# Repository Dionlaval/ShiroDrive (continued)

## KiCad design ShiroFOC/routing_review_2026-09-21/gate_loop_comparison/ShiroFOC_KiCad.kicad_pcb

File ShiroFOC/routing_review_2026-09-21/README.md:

# Routing review checkpoint — 21 September 2026

**Paused for the user's visual review. Nothing here is a finished PCB.** Original P0, P1 placement and all routing candidates are preserved. No more routing changes should be made until the user provides their hint or asks to resume.

## Which board to open

| Project folder | Purpose | Unconnected items | Other error-severity DRC violations |
|---|---|---:|---:|
| `latest_trial` | Latest placement/corridor experiment; open this first | 152 | 0 |
| `best_baseline` | Most complete checked connectivity before the corridor reset | 91 | 0 |
| `gate_loop_comparison` | Seven gate/reference connections, but some outgoing/return routes form large loops; comparison only | 149 | 0 |

Open `ShiroFOC_KiCad.kicad_pro` or `.kicad_pcb` in each folder. Each includes the schematic hierarchy, local libraries, board rules and native DRC checkpoint. Counts refer to KiCad's unconnected **items**, not distinct nets. Zero other errors does not mean clean DRC: all boards remain incomplete and have warnings.

## Most useful area to examine

The corridor from U301's upper/right gate-driver pins to Q401/Q402/Q403 and their gate resistors. In native KiCad coordinates this is approximately **X 137–170 mm, Y 128–164 mm** (board-local X 37–70, Y 28–64).

- Highlight **GHS1 + OUT1**, **GHS2 + OUT2**, and **GHS3 + OUT3** in turn. Each high-side gate signal needs its matching phase-reference return close by.
- Check the remaining **GLS1/2/3** routes alongside their source/ground return environment.
- The six **SHUNT_*_SENSE_P/N** traces and underside ratio networks are already connected; preserve their Kelvin pickoff and avoid routing gate signals alongside them for long distances.
- Examine C412/C422/C432 and the adjacent source/shunt via banks on both faces. A passage that appears open on top may be blocked underneath.
- Preserve the wide **VM** feed and the **FORCE_P** / shunt / GND current paths. A route that cuts their only useful copper bridge is not an acceptable improvement.

A useful hint would be a preferred routing corridor, a different ordering of these paths, or a suggested relocation of the MCU-side parts / phase-cell passives. No need to solve all remaining ordinary signals.

## What the latest trial contains

- Ordinary unlocked routes around the driver corridor were removed deliberately. This explains the higher unconnected count than the baseline.
- R301 and C306 moved to open an underside corridor; R602 retained at the earlier clean location. GHS1/GHS3 outward fanouts and additional driver fanouts remain.
- C412/C422/C432 were rotated horizontally; their VM/GND via arrangements changed. Six gate resistors moved 0.2 mm sideways to maintain component courtyards.
- Local 0.20 mm clearance regions were added around those populated capacitor/gate-resistor areas. Existing global and MCU/package rules remain.
- The middle-phase reference route was previously trapped. It now has a roughly 23.5 mm new connecting path. All three OUT reference connections are present in this latest trial, but their matching gate routes still need to be established as close pairs.
- Remaining warnings include narrow copper connections around the revised via arrays, dangling items and inherited silk/library warnings. These have **not** been accepted as final.

## Why routing is paused

Repeated shortest-path routing was reducing connectivity counts without preserving gate-return geometry. Some routes were rejected for 90–154 mm detours; others connected successfully but created large loops or isolated power copper. The experiments found specific placement bottlenecks, but a visual hint is now more efficient than another automatic iteration.

## Still outstanding after the hint

Finish paired gate routing and ordinary signals; restore/check bus copper continuity and ground stitching; recheck native DRC and schematic/PCB parity; perform the critical return-path/EMI/thermal review; implement low-tradeoff high-priority fixes; produce the requested actual-PCB wireframe and colour-coded routing presentation. External fabricator and component-availability checks remain excluded as requested.

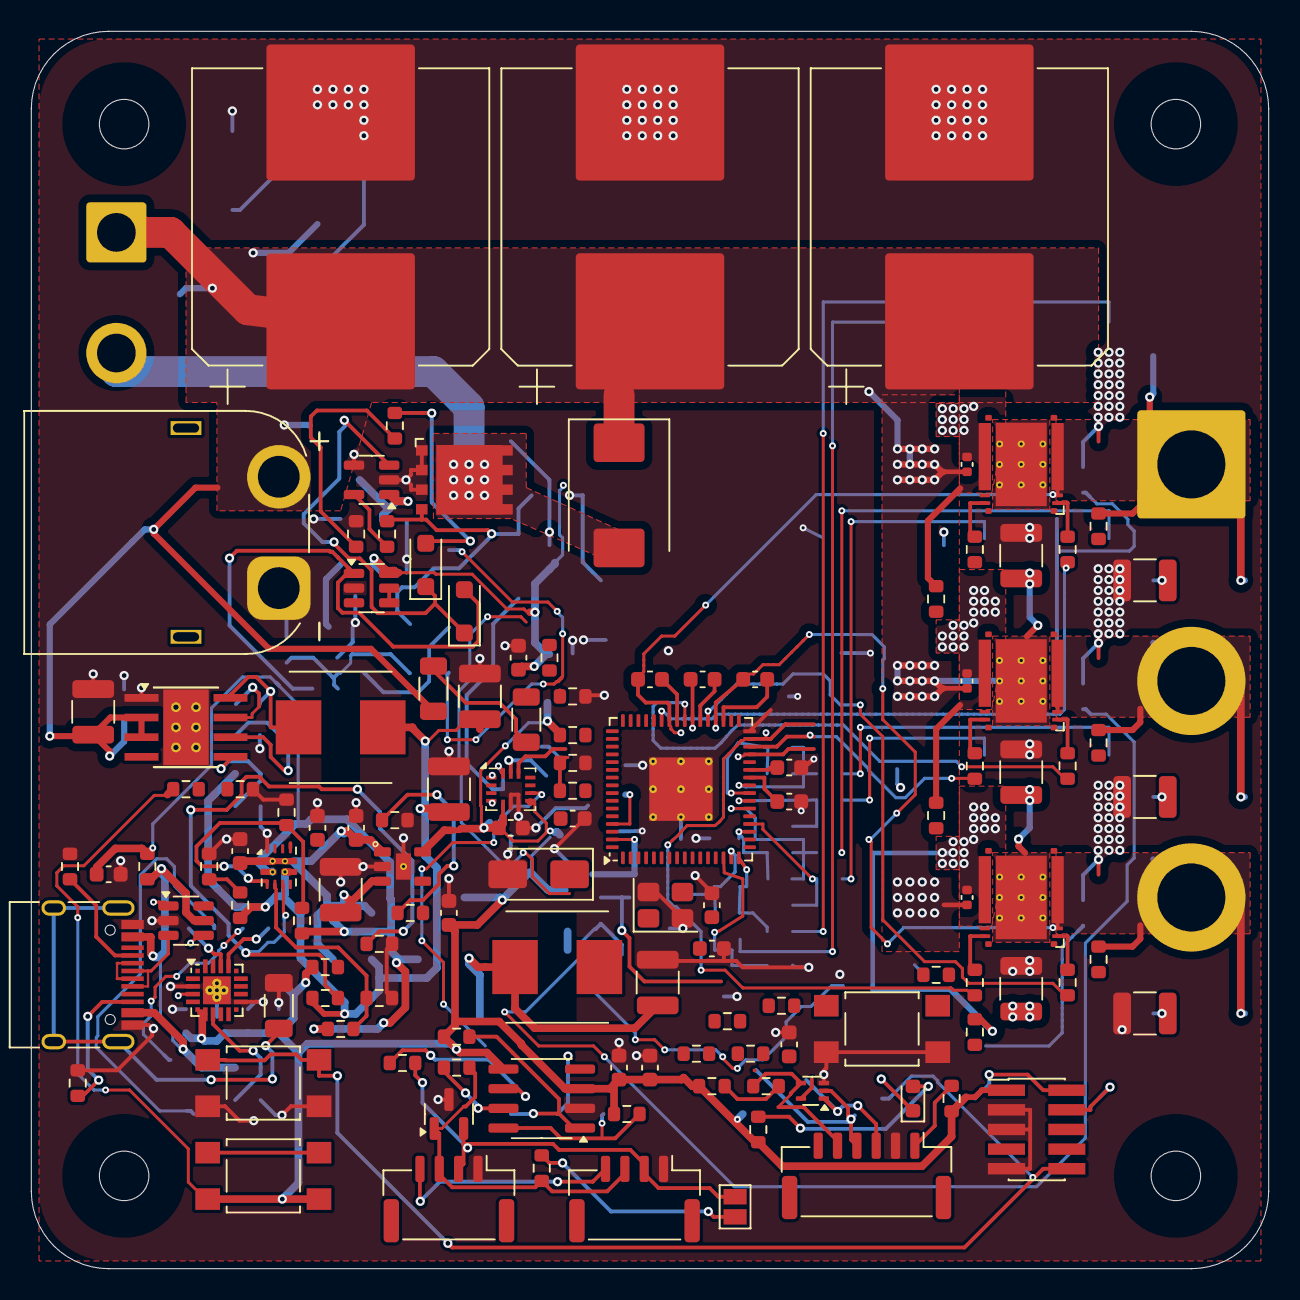
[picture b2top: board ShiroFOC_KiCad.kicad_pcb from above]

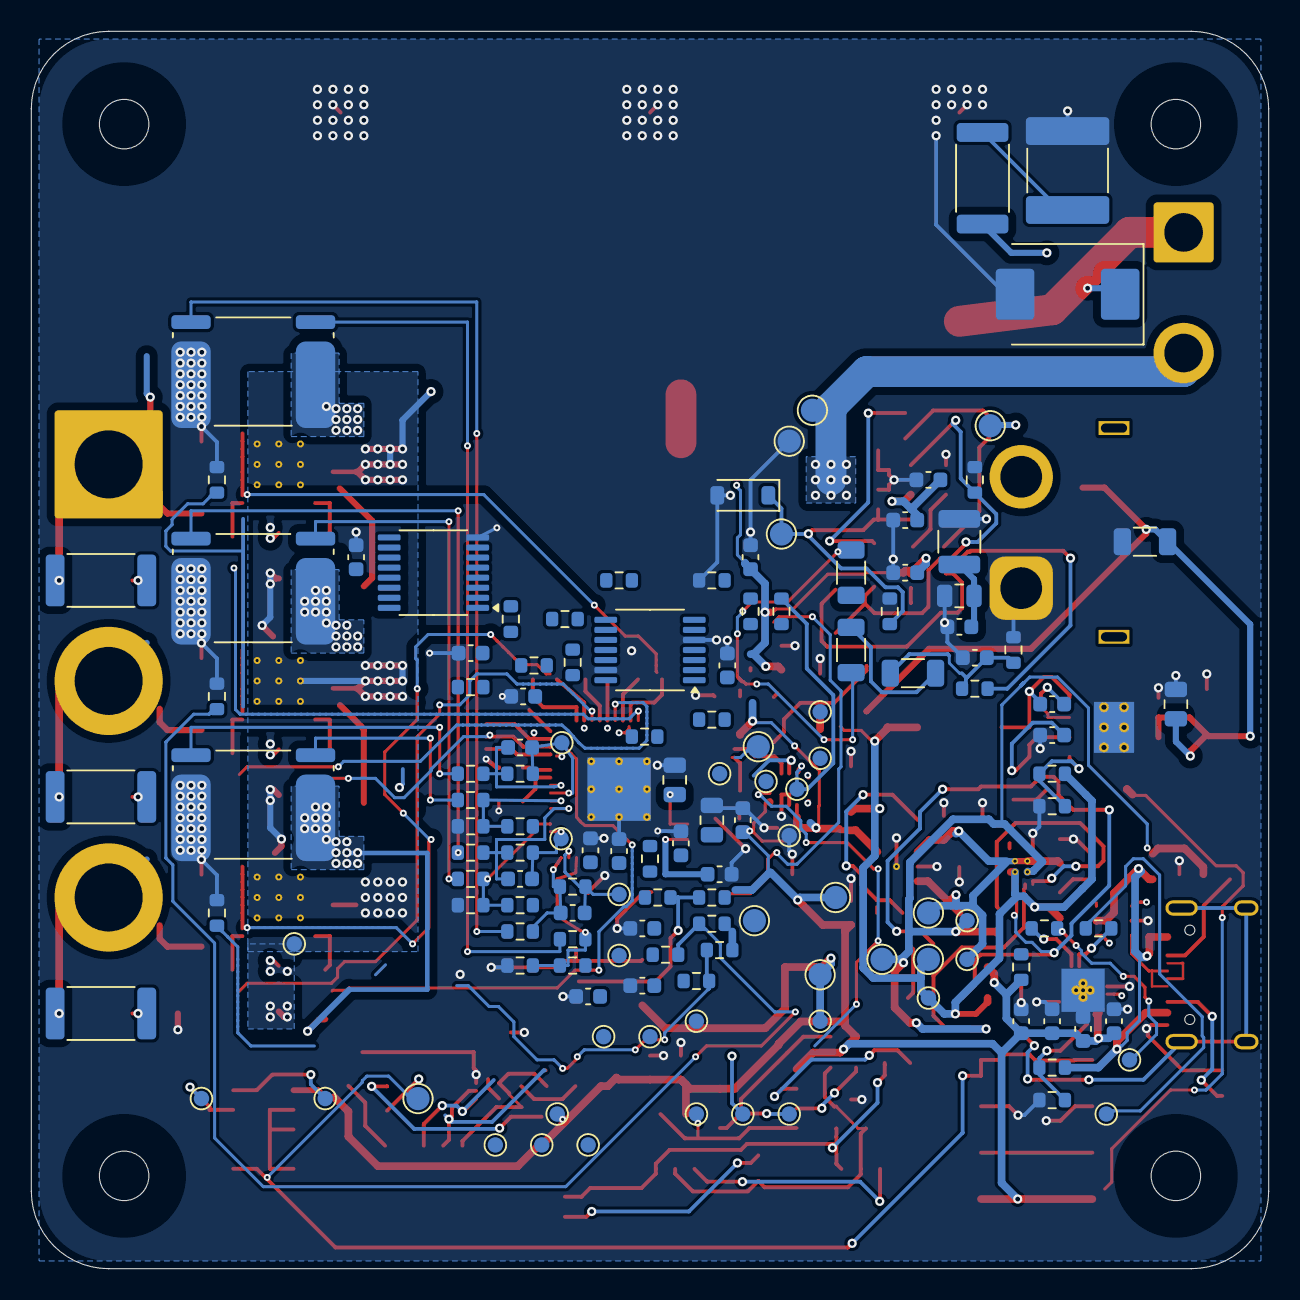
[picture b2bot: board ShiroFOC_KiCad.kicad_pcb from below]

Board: 4 copper layers, 80.0 x 80.0 mm, 264 parts (136 on the bottom side), 148 nets.

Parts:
C101, C102, C103: 680uF 63V; CP_Elec_18x17.5
C104: 4.7uF 100V X7R; C_1210_3225Metric
C105: 100nF 100V X7R; C_0805_2012Metric
C106: 10nF 100V C0G; C_0603_1608Metric
C107: RC DAMP C - TUNE; C_2220_5750Metric
C108, C314, C711, C712, C713: 10nF; C_0603_1608Metric
C201: 2.2uF 100V X7R; C_1210_3225Metric
C202: 220nF 100V X7R; C_0805_2012Metric
C203, C209, C211, C301, C303, C305, C307, C310, C503, C601, C603, C701, C702, C801, C902, C904: 100nF; C_0603_1608Metric
C204, C304, C306, C602, C802: 1uF; C_0603_1608Metric
C205, C206, C210: 22uF 10V X7R; C_1210_3225Metric
C207: 4.7nF 2kV; C_1206_3216Metric
C208: 1uF 10V; C_0603_1608Metric
C212, C213: 2.2uF 10V X7R; C_0603_1608Metric
C302: 10uF 10V; C_0805_2012Metric
C308, C309: 10pF C0G; C_0603_1608Metric
C311: 220nF 100V; C_0805_2012Metric
C312: 10uF 25V X7R; C_1210_3225Metric
C313, C411, C421, C431, C502: 100nF 25V; C_0603_1608Metric
C412, C422, C432: 1uF 100V X7R; C_1210_3225Metric
C413, C423, C433: SNUBBER C TUNE; C_1210_3225Metric
C414, C424, C434: 47pF C0G; C_0603_1608Metric
C415, C425, C435: 10nF 100V X7S; C_0402_1005Metric
C501: 1uF 25V; C_0603_1608Metric
C504: 1nF C0G; C_0603_1608Metric
C604: 100nF 50V; C_0603_1608Metric
C901, C903: 4.7uF 10V; C_0603_1608Metric
D101: VM TVS - SELECT AFTER TEST; D_SMC
D301: RED; LED_0603_1608Metric
D302: STPS1H100A; D_SMA
D501: BZT52C12 12V; D_SOD-123
D502, D503: BAT54H; D_SOD-123F
D504: B5100C 100V 5A; D_SMC
D601: TPD3E001DRLR 3-line ESD; Texas_R-PDSO-N5_DRL-5
D801: PESD2CANFD24V-T; SOT-23
H1, H2, H3, H4: M3 NPTH; MountingHole_3.2mm_M3
J101: AMASS XT60PW-M; AMASS_XT60PW-M_1x02_P7.20mm_Horizontal
J201: USB-C service; USB_C_Receptacle_HRO_TYPE-C-31-M-12
J401: MOTOR U/V/W; SolderWire-6sqmm_1x03_P14mm_D3.5mm_OD7mm
J501: BRAKE RESISTOR; SolderWire-2sqmm_1x02_P7.8mm_D2mm_OD3.9mm
J601: EXT ENCODER / HALL; JST_GH_BM06B-GHS-TBT_1x06-1MP_P1.25mm_Vertical
J801: CAN 1; JST_GH_BM04B-GHS-TBT_1x04-1MP_P1.25mm_Vertical
J802: CAN 2; JST_GH_BM04B-GHS-TBT_1x04-1MP_P1.25mm_Vertical
J1001: ARM Cortex SWD 10-pin; PinHeader_2x05_P1.27mm_Vertical_SMD
JP801: TERM ENABLE; SolderJumper-2_P1.3mm_Open_Pad1.0x1.5mm
L201, L301: 22uH / 2.75A; WE_LHMI_7050_74437349220
Q401, Q402, Q403: CSD88599Q5DC; CSD88599Q5DC_DMM0022A
Q501: CSD19531Q5A 100V; CSD19531Q5A_Q5A_DQJ0008A
R101: 470k 0.25W; R_1206_3216Metric
R102: RC DAMP R - TUNE; R_2512_6332Metric
R103, R104: 270k 0.1% 100V; R_1206_3216Metric
R105: 27k 0.1%; R_0603_1608Metric
R106, R304, R312, R711, R712, R713, R901, R1001: 1k; R_0603_1608Metric
R201: 100k 1%; R_0603_1608Metric
R202: 24.9k 1%; R_0603_1608Metric
R203, R204: 5.1k; R_0603_1608Metric
R205, R301, R302, R412, R422, R432: 0R; R_0603_1608Metric
R206: 15.0k 1%; R_0603_1608Metric
R207, R209, R211, R213: 5.10k 1%; R_0603_1608Metric
R208: 10.0k 1%; R_0603_1608Metric
R210, R212: 21.0k 1%; R_0603_1608Metric
R214: 80.6k 1%; R_0603_1608Metric
R215, R305, R306, R307, R308, R309, R311, R501, R504, R505, R801, R805: 10k; R_0603_1608Metric
R303, R310, R413, R414, R423, R424, R433, R434: 100k; R_0603_1608Metric
R313, R314: 22R; R_0603_1608Metric
R410, R420, R430, R441, R442, R443: 56k 0.1%; R_0603_1608Metric
R411, R421, R431, R503: 4.7R; R_0603_1608Metric
R415, R425, R435: SNUBBER R TUNE; R_2512_6332Metric
R416, R426, R436: BVR-Z-R0005 0.5mR; R_Shunt_Isabellenhuette_BVR4026
R417, R418, R427, R428, R437, R438: 1k 0.1%; R_0603_1608Metric
R419, R429, R439: 28k 0.1%; R_0603_1608Metric
R502, R601, R602, R603, R611, R714: 33R; R_0603_1608Metric
R506, R507, R508: 150k 0.1% 100V; R_1206_3216Metric
R509: 12.7k 0.1%; R_0603_1608Metric
R510: 1M 0.1%; R_0603_1608Metric
R604: 0R; external load <=25mA; R_0603_1608Metric
R605, R606, R607, R902, R903: 100R; R_0603_1608Metric
R608, R609, R610: 10k DNP Hall pull-up; R_0603_1608Metric
R701, R702, R703: 4.7k 1%; R_0603_1608Metric
R802: 120R 1%; R_0603_1608Metric
R803: 0R CANH link; R_0603_1608Metric
R804: 0R CANL link; R_0603_1608Metric
R904: 22.1k 1%; R_0603_1608Metric
R905: 47.5k 1%; R_0603_1608Metric
SW301, SW1002: RESET; SW_SPST_TL3305A
SW1001: BOOT0; SW_SPST_TL3305A
TH701, TH702, TH703: 10k NTC B3380; R_0603_1608Metric
TP101: VM; TestPoint_Pad_D1.5mm
TP102: GND; TestPoint_Pad_D1.5mm
TP103: VBUS_SENSE; TestPoint_Pad_D1.5mm
TP201: 5V_BAT; TestPoint_Pad_D1.5mm
TP202: 5V_USB; TestPoint_Pad_D1.5mm
TP203: 5V_SYS; TestPoint_Pad_D1.5mm
TP204: 3V3; TestPoint_Pad_D1.5mm
TP301: VCC; TestPoint_Pad_D1.5mm
TP302: SCREF; TestPoint_Pad_D1.5mm
TP303: NRST; TestPoint_Pad_D1.5mm
TP501: BRAKE_GATE; TestPoint_Pad_D1.5mm
TP502: BRK_SW; TestPoint_Pad_D1.5mm
TP701: NTC_A; TestPoint_Pad_D1.0mm
TP702: NTC_B; TestPoint_Pad_D1.0mm
TP703: NTC_C; TestPoint_Pad_D1.0mm
TP901: USB_UART_TX; TestPoint_Pad_D1.0mm
TP902: USB_UART_RX; TestPoint_Pad_D1.0mm
TP903: GND; TestPoint_Pad_D1.0mm
TP1001: VM; TestPoint_Pad_D1.0mm
TP1002: VCC; TestPoint_Pad_D1.0mm
TP1003: 5V_BAT; TestPoint_Pad_D1.0mm
TP1004: 5V_USB; TestPoint_Pad_D1.0mm
TP1005: 5V_SYS; TestPoint_Pad_D1.0mm
TP1006: 3V3; TestPoint_Pad_D1.0mm
TP1007: NRST; TestPoint_Pad_D1.0mm
TP1008: SWDIO; TestPoint_Pad_D1.0mm
TP1009: SWCLK; TestPoint_Pad_D1.0mm
TP1010: SPI3_SCK; TestPoint_Pad_D1.0mm
TP1011: SPI3_MISO; TestPoint_Pad_D1.0mm
TP1012: SPI3_MOSI; TestPoint_Pad_D1.0mm
TP1013: FDCAN1_TX; TestPoint_Pad_D1.0mm
TP1014: FDCAN1_RX; TestPoint_Pad_D1.0mm
TP1015: FEEDBACK_A_H1; TestPoint_Pad_D1.0mm
TP1016: FEEDBACK_B_H2; TestPoint_Pad_D1.0mm
TP1018: OPO_U1; TestPoint_Pad_D1.0mm
TP1019: OPO_V1; TestPoint_Pad_D1.0mm
TP1020: OPO_W1; TestPoint_Pad_D1.0mm
TP1021: SPARE_GPIO_1; TestPoint_Pad_D1.0mm
TP1022: CAN_STB; TestPoint_Pad_D1.0mm
TP1023: SPARE_GPIO_3; TestPoint_Pad_D1.0mm
TP1024: SPARE_TIM_GPIO; TestPoint_Pad_D1.0mm
U201: LMR36510FADDAR; Texas_HTSOP-8-1EP_3.9x4.9mm_P1.27mm_EP2.95x4.9mm_Mask2.4x3.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
U202: USBLC6-2SC6; SOT-23-6
U203: TPS2121RUXR; Texas_VQFN-HR-12_2x2.5mm_P0.5mm_ThermalVias
U204: TLV75533PDYDR; Texas_DYD0005A_SOT23-5
U301: STSPIN32G4; QFN-64-1EP_9x9mm_P0.5mm_EP4.1x4.1mm_ThermalVias
U501: UCC27517ADBVR; SOT-23-5
U502: TLV3012BIDBVR; SOT-23-6
U601: AS5047P-ATSM; TSSOP-14_4.4x5mm_P0.65mm
U602: TMUX1574PW; TSSOP-16_4.4x5mm_P0.65mm
U701: BMI323; Bosch_LGA-14_3x2.5mm_P0.5mm
U801: TCAN3413DR; SOIC-8_3.9x4.9mm_P1.27mm
U901: CP2102N-A02-GQFN20; SiliconLabs_QFN-20-1EP_3x3mm_P0.5mm_EP1.8x1.8mm_ThermalVias
Y301: 24MHz 7pF; Crystal_SMD_3225-4Pin_3.2x2.5mm

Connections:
3V3: C213.1, C301.1, C302.1, C307.1, C503.1, C601.1, C602.1, C603.1, C701.1, C702.1, C801.1, C802.1, C901.1, C902.1, C903.1, C904.1, J1001.1, R215.1, R301.1, R303.1, R304.1, R305.1, R308.1, R309.1, R310.1, R604.1, R608.1, R609.1, R610.1, R701.1, R702.1, R703.1, R801.1, R805.1, R901.1, SW1001.2, TP204.1, TP1006.1, U204.5, U301.1, U301.2, U301.64, U502.6, U601.11, U601.12, U602.16, U701.5, U701.8, U801.3, U801.5, U901.6, U901.7
5V_BAT: C205.1, C206.1, L201.2, R201.1, R206.1, R210.1, TP201.1, TP1003.1, U203.7
5V_SYS: C210.1, C211.1, C212.1, TP203.1, TP1005.1, U203.1, U203.8, U204.1, U204.3
5V_USB: C208.1, R205.2, R208.1, R212.1, TP202.1, TP1004.1, U203.2
5V_USB_RAW: J201.A4, J201.A9, J201.B4, J201.B9, R205.1, R904.1, U202.5
/5 V / 3.3 V power/5V_FB: R201.2, R202.1, U201.5
/Brake chopper/BRAKE_OV_CMD: D503.2, R510.1, U502.1
/Brake chopper/BRAKE_PWM_DRV: D502.1, D503.1, R505.1, U501.3
/CAN interface/CANH_BUS: D801.1, J801.3, J802.3, R802.1, R803.2
/CAN interface/CANH_INT: R803.1, U801.7
/CAN interface/CANL_BUS: D801.2, J801.2, J802.2, JP801.2, R804.2
/CAN interface/CANL_INT: R804.1, U801.6
/CAN interface/CAN_SHIELD: J801.4, J802.4
/CAN interface/CAN_TERM_MID: JP801.1, R802.2
/Current / temperature/NTC_A_RAW: R701.2, R711.1, TH701.1
/Current / temperature/NTC_B_RAW: R702.2, R712.1, TH702.1
/Current / temperature/NTC_C_RAW: R703.2, R713.1, TH703.1
/Current / temperature/OPN_U1: C414.2, R418.2, R419.2, U301.16
/Current / temperature/OPN_V1: C424.2, R428.2, R429.2, U301.22
/Current / temperature/OPN_W1: C434.2, R438.2, R439.2, U301.25
/Current / temperature/OPP_U1: R410.2, R417.2, R441.1, U301.14
/Current / temperature/OPP_V1: R420.2, R427.2, R442.1, U301.20
/Current / temperature/OPP_W1: R430.2, R437.2, R443.1, U301.23
/Feedback selection/3V3_EXT_FB: J601.1, R604.2
/Feedback selection/FB_ESD_RAIL: C604.1, D601.5
/Feedback selection/MUX_EXT_A: R605.2, R608.2, U602.3
/Feedback selection/MUX_EXT_B: R606.2, R609.2, U602.6
/Feedback selection/MUX_EXT_I: R607.2, R610.2, U602.10
/MCU / clock / SWD/NRST: C310.1, J1001.10, R303.2, SW301.1, SW1002.1, TP303.1, TP1007.1, U301.8
/MCU / clock / SWD/SPARE_GPIO_1: TP1021.1, U301.5
/MCU / clock / SWD/SPARE_GPIO_3: TP1023.1, U301.3
/MCU / clock / SWD/SPARE_TIM_GPIO: TP1024.1, U301.44
/SPI sensors/AS5047_MISO_RAW: R611.1, U601.3
/SPI sensors/BMI323_MISO_RAW: R714.1, U701.1
/SPI sensors/ENC_ON_A: R601.1, U601.7
/SPI sensors/ENC_ON_B: R602.1, U601.6
/SPI sensors/ENC_ON_I: R603.1, U601.14
/SPI sensors/SPI3_MOSI: R314.2, TP1012.1, U601.4, U701.14
/SPI sensors/SPI3_SCK: R313.2, TP1010.1, U601.2, U701.13
/Three-phase bridge/SHUNT_U_FORCE_P: C415.2, Q401.12, Q401.13, Q401.14, Q401.15, Q401.16, Q401.17, Q401.18, Q401.19, Q401.20, R414.2, R416.1
/Three-phase bridge/SHUNT_V_FORCE_P: C425.2, Q402.12, Q402.13, Q402.14, Q402.15, Q402.16, Q402.17, Q402.18, Q402.19, Q402.20, R424.2, R426.1
/Three-phase bridge/SHUNT_W_FORCE_P: C435.2, Q403.12, Q403.13, Q403.14, Q403.15, Q403.16, Q403.17, Q403.18, Q403.19, Q403.20, R434.2, R436.1
/USB service/CP2102_RST_N: R901.2, U901.9
/USB service/CP2102_VBUS_SENSE: R904.2, R905.1, U901.8
/USB service/UART_BRIDGE_RX: R903.2, U901.17
/USB service/UART_BRIDGE_TX: R902.1, U901.18
/USB service/USB_CC1: J201.A5, R203.1
/USB service/USB_CC2: J201.B5, R204.1
/USB service/USB_DM: U202.6, U901.5
/USB service/USB_DM_CONN: J201.A7, J201.B7, U202.1
/USB service/USB_DP: U202.4, U901.4
/USB service/USB_DP_CONN: J201.A6, J201.B6, U202.3
/USB service/USB_SHIELD: C207.1, J201.S1
AS5047P_CS_N: R309.2, U301.51, U601.1
BOOT1: C411.1, U301.41
BOOT2: C421.1, U301.38
BOOT3: C431.1, U301.35
BRAKE_PWM: R501.1, R502.1, U301.60
CAN_STB: R801.2, TP1022.1, U301.28, U801.8
FDCAN1_RX: TP1014.1, U301.47, U801.4
FDCAN1_TX: R805.2, TP1013.1, U301.48, U801.1
FEEDBACK_A_H1: TP1015.1, U301.57, U602.4
FEEDBACK_B_H2: TP1016.1, U301.58, U602.7
FEEDBACK_ENABLE_N: R305.2, U301.4, U602.15
FEEDBACK_I_H3: R307.1, R1001.1, U301.59, U602.9
FEEDBACK_SELECT: R306.1, U301.53, U602.1
GHS1: R411.1, U301.43
GHS2: R421.1, U301.40
GHS3: R431.1, U301.37
GLS1: R412.1, U301.29
GLS2: R422.1, U301.30
GLS3: R432.1, U301.31
GND: C101.2, C102.2, C103.2, C104.2, C105.2, C106.2, C107.2, C108.2, C201.2, C202.2, C204.2, C205.2, C206.2, C207.2, C208.2, C209.2, C210.2, C211.2, C212.2, C213.2, C301.2, C302.2, C303.2, C304.2, C305.2, C306.2, C307.2, C308.2, C309.2, C310.2, C311.2, C312.2, C313.2, C314.2, C412.2, C413.2, C422.2, C423.2, C432.2, C433.2, C501.2, C502.2, C503.2, C504.2, C601.2, C602.2, C603.2, C604.2, C701.2, C702.2, C711.2, C712.2, C713.2, C801.2, C802.2, C901.2, C902.2, C903.2, C904.2, D101.2, D302.2, D501.2, D601.3, D801.3, J101.1, J201.A1, J201.A12, J201.B1, J201.B12, J601.2, J801.1, J802.1, J1001.3, J1001.5, J1001.9, Q501.1, Q501.2, Q501.3, R101.2, R105.2, R202.2, R203.2, R204.2, R207.2, R209.2, R211.2, R213.2, R214.2, R306.2, R307.2, R311.2, R416.4, R426.4, R436.4, R441.2, R442.2, R443.2, R501.2, R504.2, R505.2, R509.2, R905.2, SW301.2, SW1002.2, TH701.2, TH702.2, TH703.2, TP102.1, TP903.1, U201.1, U201.9, U202.2, U203.12, U204.2, U301.32, U301.65, U501.2, U501.4, U502.2, U601.5, U601.13, U602.8, U701.6, U701.7, U801.2, U901.3, U901.12, U901.21, Y301.2, Y301.4
IMU_CS_N: R308.2, U301.21, U701.12
IMU_INT1: U301.17, U701.4
IMU_INT2: U301.18, U701.9
MUX_ON_A: R601.2, U602.2
MUX_ON_B: R602.2, U602.5
MUX_ON_I: R603.2, U602.11
NTC_PHASE_A: C711.1, R711.2, TP701.1, U301.12
NTC_PHASE_B: C712.1, R712.2, TP702.1, U301.9
NTC_PHASE_C: C713.1, R713.2, TP703.1, U301.10
unnamed: C107.1, R102.2
unnamed: C413.1, R415.2
unnamed: C423.1, R425.2
unnamed: C433.1, R435.2
unnamed: D301.2, R304.2
unnamed: D301.1, U301.11
unnamed: D302.1, L301.1, U301.62
unnamed: D501.1, Q501.4, R503.2, R504.1, TP501.1
unnamed: D502.2, R502.2
unnamed: D504.2, J501.2, Q501.5, Q501.6, Q501.7, Q501.8, TP502.1
unnamed: D601.1, J601.3, R605.1
unnamed: D601.2, J601.4, R606.1
unnamed: D601.4, J601.5, R607.1
unnamed: Q401.1, R411.2, R413.1
unnamed: Q401.22, R412.2, R414.1
unnamed: Q402.1, R421.2, R423.1
unnamed: Q402.22, R422.2, R424.1
unnamed: Q403.1, R431.2, R433.1
unnamed: Q403.22, R432.2, R434.1
unnamed: R103.2, R104.1
unnamed: R104.2, R105.1, R106.1
unnamed: R310.2, R311.1, R312.1
unnamed: R506.2, R507.1
unnamed: R507.2, R508.1
unnamed: R1001.2, SW1001.1
unnamed: C203.1, U201.7
unnamed: C203.2, L201.1, U201.8
unnamed: C204.1, U201.6
unnamed: R208.2, R209.1, U203.3
unnamed: R214.1, U203.10
unnamed: R210.2, R211.1, U203.5
unnamed: R212.2, R213.1, U203.4
unnamed: R206.2, R207.1, U203.6
unnamed: C209.1, U203.11
unnamed: J1001.2, TP1008.1, U301.49
unnamed: J1001.4, TP1009.1, U301.50
unnamed: C308.1, U301.6, Y301.1
unnamed: C309.1, U301.7, Y301.3
unnamed: C314.1, R312.2, TP302.1, U301.52
unnamed: R503.1, U501.5
unnamed: C504.1, R508.2, R509.1, R510.2, U502.3
unnamed: U502.4, U502.5
OPO_U1: C414.1, R419.1, TP1018.1, U301.15
OPO_V1: C424.1, R429.1, TP1019.1, U301.19
OPO_W1: C434.1, R439.1, TP1020.1, U301.24
OUT1: C411.2, J401.1, Q401.2, Q401.3, Q401.4, Q401.5, Q401.6, Q401.7, Q401.8, Q401.9, Q401.10, Q401.11, R413.2, R415.1, U301.42
OUT2: C421.2, J401.2, Q402.2, Q402.3, Q402.4, Q402.5, Q402.6, Q402.7, Q402.8, Q402.9, Q402.10, Q402.11, R423.2, R425.1, U301.39
OUT3: C431.2, J401.3, Q403.2, Q403.3, Q403.4, Q403.5, Q403.6, Q403.7, Q403.8, Q403.9, Q403.10, Q403.11, R433.2, R435.1, U301.36
PWR_SOURCE_STATUS: R215.2, U203.9
SHUNT_U_SENSE_N: R416.3, R418.1
SHUNT_U_SENSE_P: R416.2, R417.1
SHUNT_V_SENSE_N: R426.3, R428.1
SHUNT_V_SENSE_P: R426.2, R427.1
SHUNT_W_SENSE_N: R436.3, R438.1
SHUNT_W_SENSE_P: R436.2, R437.1
SPI3_MISO: R611.2, R714.2, TP1011.1, U301.55
SPI3_MOSI_MCU: R314.1, U301.56
SPI3_SCK_MCU: R313.1, U301.54
USB_UART_RX: R902.2, TP902.1, U301.46
USB_UART_TX: R903.1, TP901.1, U301.45
VBUS_MUX_IN: R106.2, U602.13, U602.14
VBUS_SENSE: C108.1, TP103.1, U301.13, U602.12
VCC: C312.1, C313.1, C501.1, C502.1, L301.2, TP301.1, TP1002.1, U301.63, U501.1
VDDA: C303.1, C304.1, R301.2, R302.1, U301.27
VM: C101.1, C102.1, C103.1, C104.1, C105.1, C106.1, C201.1, C202.1, C311.1, C412.1, C415.1, C422.1, C425.1, C432.1, C435.1, D101.1, D504.1, J101.2, J501.1, Q401.27, Q402.27, Q403.27, R101.1, R102.1, R103.1, R506.1, TP101.1, TP1001.1, U201.2, U201.3, U301.61
VREF+: C305.1, C306.1, R302.2, R410.1, R420.1, R430.1, U301.26

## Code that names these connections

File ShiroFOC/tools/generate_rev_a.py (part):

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
# STSPIN32G4 exact package pin names.
st_names = {
    1:"REG3V3/VDD",2:"VBAT",3:"PC13",4:"PC14",5:"PC15",6:"PF0",7:"PF1",8:"PG10/NRST",
    9:"PC0",10:"PC1",11:"PC2",12:"PC3",13:"PA0",14:"PA1",15:"PA2",16:"PA3",
    17:"PA4",18:"PA5",19:"PA6",20:"PA7",21:"PC4",22:"PC5",23:"PB0",24:"PB1",
    25:"PB2",26:"VREF+",27:"VDDA",28:"PB10",29:"GLS1",30:"GLS2",31:"GLS3",32:"PGND",
    33:"NC",34:"NC",35:"BOOT3",36:"OUT3",37:"GHS3",38:"BOOT2",39:"OUT2",40:"GHS2",
    41:"BOOT1",42:"OUT1",43:"GHS1",44:"PA8",45:"PA9",46:"PA10",47:"PA11",48:"PA12",
    49:"PA13/SWDIO",50:"PA14/SWCLK",51:"PA15",52:"SCREF",53:"PD2",54:"PB3",55:"PB4",56:"PB5",
    57:"PB6",58:"PB7",59:"PB8/BOOT0",60:"PB9",61:"VM",62:"SW",63:"VCC",64:"REGIN",65:"VSS/EP",
}
st_left = [(str(i), st_names[i]) for i in range(1, 33)]
st_right = [(str(i), st_names[i]) for i in range(65, 32, -1)]
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    passive(s,RES,"R204","5.1k",1300,7450,R0603,"USB_CC2","GND")
    passive(s,CAP,"C207","4.7nF 2kV",1300,8350,"Capacitor_SMD:C_1206_3216Metric","USB_SHIELD","GND",dnp=True)
    esd=s.comp(USB_ESD,"U202","USBLC6-2SC6",7000,7450,"Package_TO_SOT_SMD:SOT-23-6","https://www.st.com/resource/en/datasheet/usblc6-2.pdf",MPN="USBLC6-2SC6")
    for p,n in (("1","USB_DM_CONN"),("3","USB_DP_CONN"),("2","GND"),("6","USB_DM"),("4","USB_DP"),("5","5V_USB_RAW")): s.pin_label(esd,p,n)
    passive(s,RES,"R205","0R",9000,6800,R0603,"5V_USB_RAW","5V_USB")
    passive(s,CAP,"C208","1uF 10V",9000,7700,C0603,"5V_USB","GND")

    mux=s.comp(TPS,"U203","TPS2121RUXR",10600,3550,"Package_DFN_QFN:Texas_VQFN-HR-12_2x2.5mm_P0.5mm_ThermalVias","https://www.ti.com/lit/ds/symlink/tps2121.pdf",MPN="TPS2121RUXR")
    for p,n in (("7","5V_BAT"),("2","5V_USB"),("6","MUX_PR1"),("3","MUX_CP2"),("5","MUX_OV1"),("4","MUX_OV2"),("1","5V_SYS"),("8","5V_SYS"),("11","MUX_SS"),("10","MUX_ILM"),("9","PWR_SOURCE_STATUS"),("12","GND")): s.pin_label(mux,p,n)
    passive(s,RES,"R206","15.0k 1%",7600,1200,R0603,"5V_BAT","MUX_PR1")
    passive(s,RES,"R207","5.10k 1%",7600,2250,R0603,"MUX_PR1","GND")
    passive(s,RES,"R208","10.0k 1%",9500,1200,R0603,"5V_USB","MUX_CP2")
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    s.note(500,400,"STSPIN32G4 CORE - EXTERNAL 3V3 MODE",90,True)
    u=s.comp(STSPIN,"U301","STSPIN32G4",7600,5200,"Package_DFN_QFN:QFN-64-1EP_9x9mm_P0.5mm_EP4.1x4.1mm_ThermalVias","../DataSheets/STSPIN32G4.pdf",MPN="STSPIN32G4")
    pin_nets={
        1:"3V3",2:"3V3",3:"SPARE_GPIO_3",4:"FEEDBACK_ENABLE_N",5:"SPARE_GPIO_1",6:"HSE_OSC_IN",7:"HSE_OSC_OUT",8:"NRST",
        9:"NTC_PHASE_B",10:"NTC_PHASE_C",11:"STATUS_LED_RED",12:"NTC_PHASE_A",13:"VBUS_SENSE",14:"OPP_U1",15:"OPO_U1",16:"OPN_U1",
        17:"IMU_INT1",18:"IMU_INT2",19:"OPO_V1",20:"OPP_V1",21:"IMU_CS_N",22:"OPN_V1",23:"OPP_W1",24:"OPO_W1",25:"OPN_W1",
        26:"VREF+",27:"VDDA",28:"CAN_STB",29:"GLS1",30:"GLS2",31:"GLS3",32:"GND",
        35:"BOOT3",36:"OUT3",37:"GHS3",38:"BOOT2",39:"OUT2",40:"GHS2",41:"BOOT1",42:"OUT1",43:"GHS1",44:"SPARE_TIM_GPIO",
        45:"USB_UART_TX",46:"USB_UART_RX",47:"FDCAN1_RX",48:"FDCAN1_TX",49:"SWDIO",50:"SWCLK",51:"AS5047P_CS_N",52:"SCREF",
        53:"FEEDBACK_SELECT",54:"SPI3_SCK_MCU",55:"SPI3_MISO",56:"SPI3_MOSI_MCU",57:"FEEDBACK_A_H1",58:"FEEDBACK_B_H2",59:"FEEDBACK_I_H3",
        60:"BRAKE_PWM",61:"VM",62:"VCC_SW",63:"VCC",64:"3V3",65:"GND",
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    s.note(650,9400,"VCC BUCK: starts at 8 V. Firmware must set 10 V through the internal power-management interface after every VM return.")
    s.note(650,9750,"Pin 64 REGIN and pin 1 REG3V3/VDD are both tied to external 3V3. The internal 3V3 regulator stays disabled.")
    s.note(650,10100,"SCREF approx. 0.30 V controls VDS fault detection; it is not a precision current limit. Configure COMP1/2/4 + DAC + TIM1 break before enabling PWM.")
    s.note(650,10450,"PB8/BOOT0 has a 10k pulldown. FEEDBACK_ENABLE_N is pulled high, so the mux cannot drive PB8 while reset is active.")
    return s


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    add_power_block(s,"V",2,5200,5100)
    add_power_block(s,"W",3,5200,8200)
    j=s.comp(SYMS["CONN_3"],"J401","MOTOR U/V/W",15000,10500,"Connector_Wire:SolderWire-6sqmm_1x03_P14mm_D3.5mm_OD7mm")
    s.pin_label(j,"1","OUT1"); s.pin_label(j,"2","OUT2"); s.pin_label(j,"3","OUT3")
    s.note(500,10200,"LAYOUT: each gate resistor sits at its MOSFET gate. Kelvin sense traces leave pads 2/3 of each BVR shunt independently and never share force copper.")
    s.note(500,10550,"Current transfer: VOUT = VREF/2 + 28 x (SENSE_P-SENSE_N); 14 mV/A. Configure COMP1/2/4 on PA1/PA7/PB0 for hardware TIM1 break.")
    s.note(500,10900,"Fit GH=4.7R and GL=0R initially per TI guidance. Snubbers and 47 pF feedback capacitors are DNP tuning positions; bootstrap diodes are internal.")
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    s=Sheet("05_Brake_Chopper.sch","05 - Brake Chopper")
    s.note(650,500,"LOW-SIDE BRAKE CHOPPER - EXTERNAL RESISTOR",90,True)
    u=s.comp(UCC,"U501","UCC27517ADBVR",4600,3500,"Package_TO_SOT_SMD:SOT-23-5","https://www.ti.com/lit/ds/symlink/ucc27517a.pdf",MPN="UCC27517ADBVR")
    for p,n in (("1","VCC"),("2","GND"),("3","BRAKE_PWM_DRV"),("4","GND"),("5","BRAKE_GATE_DRV")): s.pin_label(u,p,n)
    passive(s,RES,"R501","10k",2200,2700,R0603,"BRAKE_PWM","GND")
    passive(s,RES,"R502","33R",3300,2700,R0603,"BRAKE_PWM","BRAKE_PWM_SER")
    passive(s,DIODE,"D502","BAT54H",4600,1800,"Diode_SMD:D_SOD-123F","BRAKE_PWM_DRV","BRAKE_PWM_SER",mpn="BAT54H,115")
    passive(s,DIODE,"D503","BAT54H",6500,1800,"Diode_SMD:D_SOD-123F","BRAKE_PWM_DRV","BRAKE_OV_CMD",mpn="BAT54H,115")
    passive(s,RES,"R505","10k",8200,1800,R0603,"BRAKE_PWM_DRV","GND")
    ov=s.comp(OVCOMP,"U502","TLV3012BIDBVR",3800,6650,"Package_TO_SOT_SMD:SOT-23-6","https://www.ti.com/lit/ds/symlink/tlv3012.pdf",MPN="TLV3012BIDBVR")
    for p,n in (("1","BRAKE_OV_CMD"),("2","GND"),("3","BRAKE_OV_SENSE"),("4","BRAKE_OV_REF"),("5","BRAKE_OV_REF"),("6","3V3")): s.pin_label(ov,p,n)
    passive(s,RES,"R506","150k 0.1% 100V",1400,4700,"Resistor_SMD:R_1206_3216Metric","VM","BRK_DIV1")
    passive(s,RES,"R507","150k 0.1% 100V",1400,5500,"Resistor_SMD:R_1206_3216Metric","BRK_DIV1","BRK_DIV2")
    passive(s,RES,"R508","150k 0.1% 100V",1400,6300,"Resistor_SMD:R_1206_3216Metric","BRK_DIV2","BRAKE_OV_SENSE")
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    s.nc(j,"6")
    passive(s,RES,"R604","0R; external load <=25mA",900,6500,R0603,"3V3","3V3_EXT_FB")
    esd=s.comp(TPD3E001,"D601","TPD3E001DRLR 3-line ESD",5100,7300,"Package_TO_SOT_SMD:Texas_R-PDSO-N5_DRL-5","https://www.ti.com/lit/ds/symlink/tpd3e001.pdf",MPN="TPD3E001DRLR")
    for p,n in (("1","EXT_A_U_CONN"),("2","EXT_B_V_CONN"),("4","EXT_I_W_CONN"),("3","GND"),("5","FB_ESD_RAIL")): s.pin_label(esd,p,n)
    passive(s,RES,"R605","100R",7300,6500,R0603,"EXT_A_U_CONN","MUX_EXT_A")
    passive(s,RES,"R606","100R",7300,7150,R0603,"EXT_B_V_CONN","MUX_EXT_B")
    passive(s,RES,"R607","100R",7300,7800,R0603,"EXT_I_W_CONN","MUX_EXT_I")
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    passive(s,CAP,"C603","100nF",14000,4700,C0603,"3V3","GND")
    passive(s,CAP,"C604","100nF 50V",5100,8450,C0603,"FB_ESD_RAIL","GND")
    s.note(500,9300,"Default: FEEDBACK_ENABLE_N high disables all outputs; FEEDBACK_SELECT low selects onboard encoder after firmware explicitly enables the mux.")
    s.note(500,9650,"MUX channel 4 isolates VBUS_SENSE when unpowered. Enable mux and wait 2 ms before reading VM; disable PWM before disabling mux. J601 pin 6 NC.")
    s.note(500,10000,"D601 pin 5 uses an isolated 100 nF ESD rail; no DC tie to 3V3. External signals: 0-3.3 V only, including when board power is off.")
    return s

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    s=Sheet("08_CAN.sch","08 - CAN / CAN-FD Interface")
    s.note(600,450,"3.3 V CAN-FD TRANSCEIVER WITH DAISY-CHAIN CONNECTORS",85,True)
    u=s.comp(TCAN,"U801","TCAN3413DR",5200,3500,"Package_SO:SOIC-8_3.9x4.9mm_P1.27mm","https://www.ti.com/lit/ds/symlink/tcan3413.pdf",MPN="TCAN3413DR")
    for p,n in (("1","FDCAN1_TX"),("4","FDCAN1_RX"),("8","CAN_STB"),("7","CANH_INT"),("6","CANL_INT"),("3","3V3"),("5","3V3"),("2","GND")): s.pin_label(u,p,n)
    passive(s,RES,"R801","10k",2300,2600,R0603,"3V3","CAN_STB")
    passive(s,RES,"R805","10k",2300,4800,R0603,"3V3","FDCAN1_TX")
    passive(s,CAP,"C801","100nF",2300,3300,C0603,"3V3","GND")
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    passive(s,RES,"R803","0R CANH link",7900,3150,R0603,"CANH_INT","CANH_BUS")
    passive(s,RES,"R804","0R CANL link",7900,3850,R0603,"CANL_INT","CANL_BUS")
    d=s.comp(CAN_ESD,"D801","PESD2CANFD24V-T",9900,3500,"Package_TO_SOT_SMD:SOT-23","https://assets.nexperia.com/documents/data-sheet/PESD2CANFD24V-T.pdf",MPN="PESD2CANFD24V-T")
    s.pin_label(d,"1","CANH_BUS"); s.pin_label(d,"2","CANL_BUS"); s.pin_label(d,"3","GND")
    passive(s,RES,"R802","120R 1%",11500,2750,R0603,"CANH_BUS","CAN_TERM_MID",dnp=True)
    passive(s,SW,"JP801","TERM ENABLE",11500,4800,"Jumper:SolderJumper-2_P1.3mm_Open_Pad1.0x1.5mm","CAN_TERM_MID","CANL_BUS",dnp=True)
    for k,x in ((1,12800),(2,14500)):
        j=s.comp(SYMS["CONN_4"],f"J80{k}",f"CAN {k}",x,3500,"Connector_JST:JST_GH_BM04B-GHS-TBT_1x04-1MP_P1.25mm_Vertical",MPN="BM04B-GHS-TBT")
        for p,n in (("1","GND"),("2","CANL_BUS"),("3","CANH_BUS"),("4","CAN_SHIELD")): s.pin_label(j,p,n)
    s.note(600,6300,"CAN_STB (PB10) has a pull-up: standby through reset. Configure FDCAN TX recessive before driving STB low. Fit termination only at bus ends.")
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
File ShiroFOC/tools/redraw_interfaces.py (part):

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        '7':(18,-8,'R'), '6':(18,16,'R'),
        '3':(-4,-24,'T'), '5':(4,-24,'T'), '2':(0,24,'B'),
    }, w=28,h=40)
    for pin,net,y in [('8','CAN_STB',55),('1','FDCAN1_TX',65),('4','FDCAN1_RX',75)]:
        p.wire((20,y),p.p('U801',pin));p.port(net,(20,y))
    p.tp('TP1022',(40,55));p.tp('TP1013',(48,65));p.tp('TP1014',(56,75))
    p.part('R801',44,39,'v');p.wire(p.p('R801','2'),(44,55))
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    for ref,x in [('C801',100),('C802',112)]:
        p.part(ref,x,36,'v');p.wire(p.p(ref,'1'),(x,28));p.supply(ref,'2','GND',dy=4)
    p.supply('U801','2','GND',dy=5)
    for ref,pin,net,y in [('R803','7','CANH_INT',63),('R804','6','CANL_INT',87)]:
        p.part(ref,120,y);p.wire(p.p('U801',pin),p.p(ref,'1'))
        p.label(net,(102,y));p.wire(p.p(ref,'2'),(184 if y==63 else 190,y))
    p.label('CANH_BUS',(128,63));p.label('CANL_BUS',(128,87))
    # Optional termination visibly spans the two bus wires.
    p.part('R802',172,69,'v');p.part('JP801',172,81,'v')
    p.wire((172,63),p.p('R802','1'));p.wire(p.p('R802','2'),p.p('JP801','1'))
    p.wire(p.p('JP801','2'),(172,87));p.label('CAN_TERM_MID',(172,75))
    p.note(150,49,'End-node option: fit R802\nand close JP801. Both DNP.',1.016)
    # Protection taps; crossings without a dot are not electrical junctions.
    p.ic('D801',149,110,{'1':(-4,-8,'T'),'2':(4,-8,'T'),'3':(0,8,'B')},w=16,h=8)
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    for ref in ['J801','J802']:
        a=p.p(ref,'1');p.wire(a,(194,a[1]),(194,a[1]+4));p.power('GND',(194,a[1]+4),up=False)
    p.wire(p.p('J801','4'),(196,81),(196,125),p.p('J802','4'))
    p.label('CAN_SHIELD',(196,95))
    p.note(12,111,'Reset state: STB high -> standby; TX high -> recessive.\nConfigure FDCAN before taking STB low.\nPlace D801 next to the connectors; route CANH/CANL together.',1.143)
    p.note(12,135,'Both headers: 1 GND | 2 CANL | 3 CANH | 4 shield/drain. Pin 4 carries no supply.',1.143)
    _position_ic_fields(p)
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    # Merge each reversible connector pair, then route as a differential pair.
    for pin in ['A6','B6']:
        a=p.p('J201',pin);p.wire(a,(68,a[1]))
    p.wire((68,65),(68,67));p.wire((68,66),(109,66));p.label('USB_DP_CONN',(75,66))
    for pin in ['A7','B7']:
        a=p.p('J201',pin);p.wire(a,(72,a[1]))
    p.wire((72,75),(72,77));p.wire((72,76),(109,76));p.label('USB_DM_CONN',(77,76))
    p.ic('U202',122,71,{'3':(-13,-5,'L'),'1':(-13,5,'L'),'4':(13,-5,'R'),'6':(13,5,'R'),'5':(0,-16,'T'),'2':(0,16,'B')},w=18,h=24)
    p.wire((70,55),p.p('U202','5'));p.supply('U202','2','GND',dy=4)
    for ref,pin,y in [('R203','A5',87),('R204','B5',97)]:
        p.part(ref,85,y);p.wire(p.p('J201',pin),p.p(ref,'1'))
        a=p.p(ref,'2');p.wire(a,(97,y));p.power('GND',(97,y),up=False)
        p.label('USB_CC1' if pin=='A5' else 'USB_CC2',(66,y))
    groundpts=[p.p('J201',pin) for pin in ['A1','A12','B1','B12']]
    for a in groundpts:p.wire(a,(a[0],111))
    p.wire((36,111),(54,111));p.power('GND',(45,111),up=False)
    p.part('C207',60,120,'v');p.wire(p.p('J201','S1'),p.p('C207','1'));p.supply('C207','2','GND',dy=4)
    p.label('USB_SHIELD',(60,110));p.note(72,114,'Shield capacitor C207 is DNP.\nPlace USBLC6 at the connector.',1.143)
    # CP2102N uses the common 3V3 rail in its documented regulator-bypass mode.
    cppins={
        '8':(-21,-22,'L'),'4':(-21,-12,'L'),'5':(-21,-4,'L'),'9':(-21,14,'L'),
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    p.note(192,23,'VREGIN and VDD: both powered from 3V3',1.143)
    p.wire(p.p('U202','4'),(150,66),(150,80),p.p('U901','4'))
    p.wire(p.p('U202','6'),(154,76),(154,88),p.p('U901','5'))
    p.label('USB_DP',(158,80));p.label('USB_DM',(158,88))
    p.part('R904',172,44,'v');p.supply('R904','1','5V_USB_RAW',dy=-6)
    p.part('R905',172,60,'v');p.wire(p.p('R904','2'),p.p('R905','1'));p.supply('R905','2','GND',dy=4)
    p.wire((172,52),(185,52),(185,70),p.p('U901','8'));p.label('CP2102_VBUS_SENSE',(185,70))
    p.part('R901',185,102,'v');p.supply('R901','1','3V3',dy=-4)
    p.wire(p.p('R901','2'),(185,106),p.p('U901','9'));p.label('CP2102_RST_N',(187,106))
    p.part('R902',265,80);p.wire(p.p('U901','18'),p.p('R902','1'));p.wire(p.p('R902','2'),(290,80));p.port('USB_UART_RX',(290,80),side='R');p.tp('TP902',(280,80))
    p.part('R903',265,88,flip=True);p.wire(p.p('U901','17'),p.p('R903','2'));p.wire(p.p('R903','1'),(290,88));p.port('USB_UART_TX',(290,88),side='R');p.tp('TP901',(280,88))
    p.label('UART_BRIDGE_TX',(247,80));p.label('UART_BRIDGE_RX',(247,88))
    for pin in ['3','12','21']:
        a=p.p('U901',pin);p.wire(a,(a[0],132))
    p.wire((221,132),(235,132));p.power('GND',(225,132),up=False);p.tp('TP903',(235,132))
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    p.heading(12,17,'SPI3: one shared bus, separate chip selects, local return damping')
    p.part('R313',36,30);p.wire((30,30),p.p('R313','1'));p.port('SPI3_SCK_MCU',(30,30))
    p.part('R314',36,42);p.wire((30,42),p.p('R314','1'));p.port('SPI3_MOSI_MCU',(30,42))
    p.wire(p.p('R313','2'),(58,30),(58,158));p.tp('TP1010',(48,30));p.label('SPI3_SCK',(48,30))
    p.wire(p.p('R314','2'),(72,42),(72,166));p.tp('TP1012',(48,42));p.label('SPI3_MOSI',(48,42))
    p.wire((30,54),(86,54),(86,174));p.port('SPI3_MISO',(30,54));p.tp('TP1011',(48,54))
    p.ic('U601',138,76,{
        '2':(-21,-10,'L'),'4':(-21,-2,'L'),'3':(-21,6,'L'),
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        for pin in (['5','13'] if u=='U601' else ['6','7']):
            a=p.p(u,pin);p.wire(a,(a[0],ground_y))
        p.wire((134,ground_y),(142,ground_y));p.power('GND',(138,ground_y),up=False)
    for u,pin,r,y,ry,net in [('U601','1','R309',60,47,'AS5047P_CS_N'),('U701','12','R308',154,141,'IMU_CS_N')]:
        p.part(r,176,ry,'v');p.supply(r,'1','3V3',dy=-4)
        p.wire(p.p(r,'2'),(176,y));p.wire(p.p(u,pin),(205,y));p.port(net,(205,y),side='R')
    for r,pin,y,src,dst in [('R601','7',72,'ENC_ON_A','MUX_ON_A'),('R602','6',80,'ENC_ON_B','MUX_ON_B'),('R603','14',88,'ENC_ON_I','MUX_ON_I')]:
        p.part(r,176,y);p.wire(p.p('U601',pin),p.p(r,'1'));p.wire(p.p(r,'2'),(205,y));p.port(dst,(205,y),side='R');p.label(src,(160,y))
    for pin,net,y in [('4','IMU_INT1',166),('9','IMU_INT2',174)]:p.wire(p.p('U701',pin),(205,y));p.port(net,(205,y),side='R')
    p.note(228,47,'ONBOARD POSITION\nABI outputs feed the selector sheet.\nTEST is tied low for normal operation.\nAlign the sensor with the shaft magnet.',1.143)
    p.note(228,140,'IMU\nMark X/Y axes on the PCB.\nKeep power-stage heat and switching\nloops away from the sensor.',1.143)
    p.note(12,191,'Place R313/R314 at the MCU. Place R611/R714 at their sensor MISO pins.\nChip-select pull-ups keep both peripherals deselected during reset.\nSPI wire crossings without a junction dot are separate nets.',1.143)
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
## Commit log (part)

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2025-07-04 Initial Commit
    Hello World!
2025-07-04 Update README.md
    added website for more info
2025-07-29 Added past development logs
    Added past development logs (evidence of initial conceptualization date)
2026-03-01 Initial Commit (Legacy archived)
    Now that I’ve graduated and gained more experience over the past few months, I’m narrowing the scope of ShiroDrive to make more consistent and steady progress.
2026-03-04 Stepper Mount Initial Prototype
2026-03-04 A3 and A4 merged
2026-03-04 minor optimizations
2026-03-16 Day 1: 3D printed brackets
2026-03-16 Day 1: revision 2
2026-04-14 3d printed updated
